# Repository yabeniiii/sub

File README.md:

# UUUV: Un-named Unmanned Underwater Vessel
early development

a remotely operated submarine

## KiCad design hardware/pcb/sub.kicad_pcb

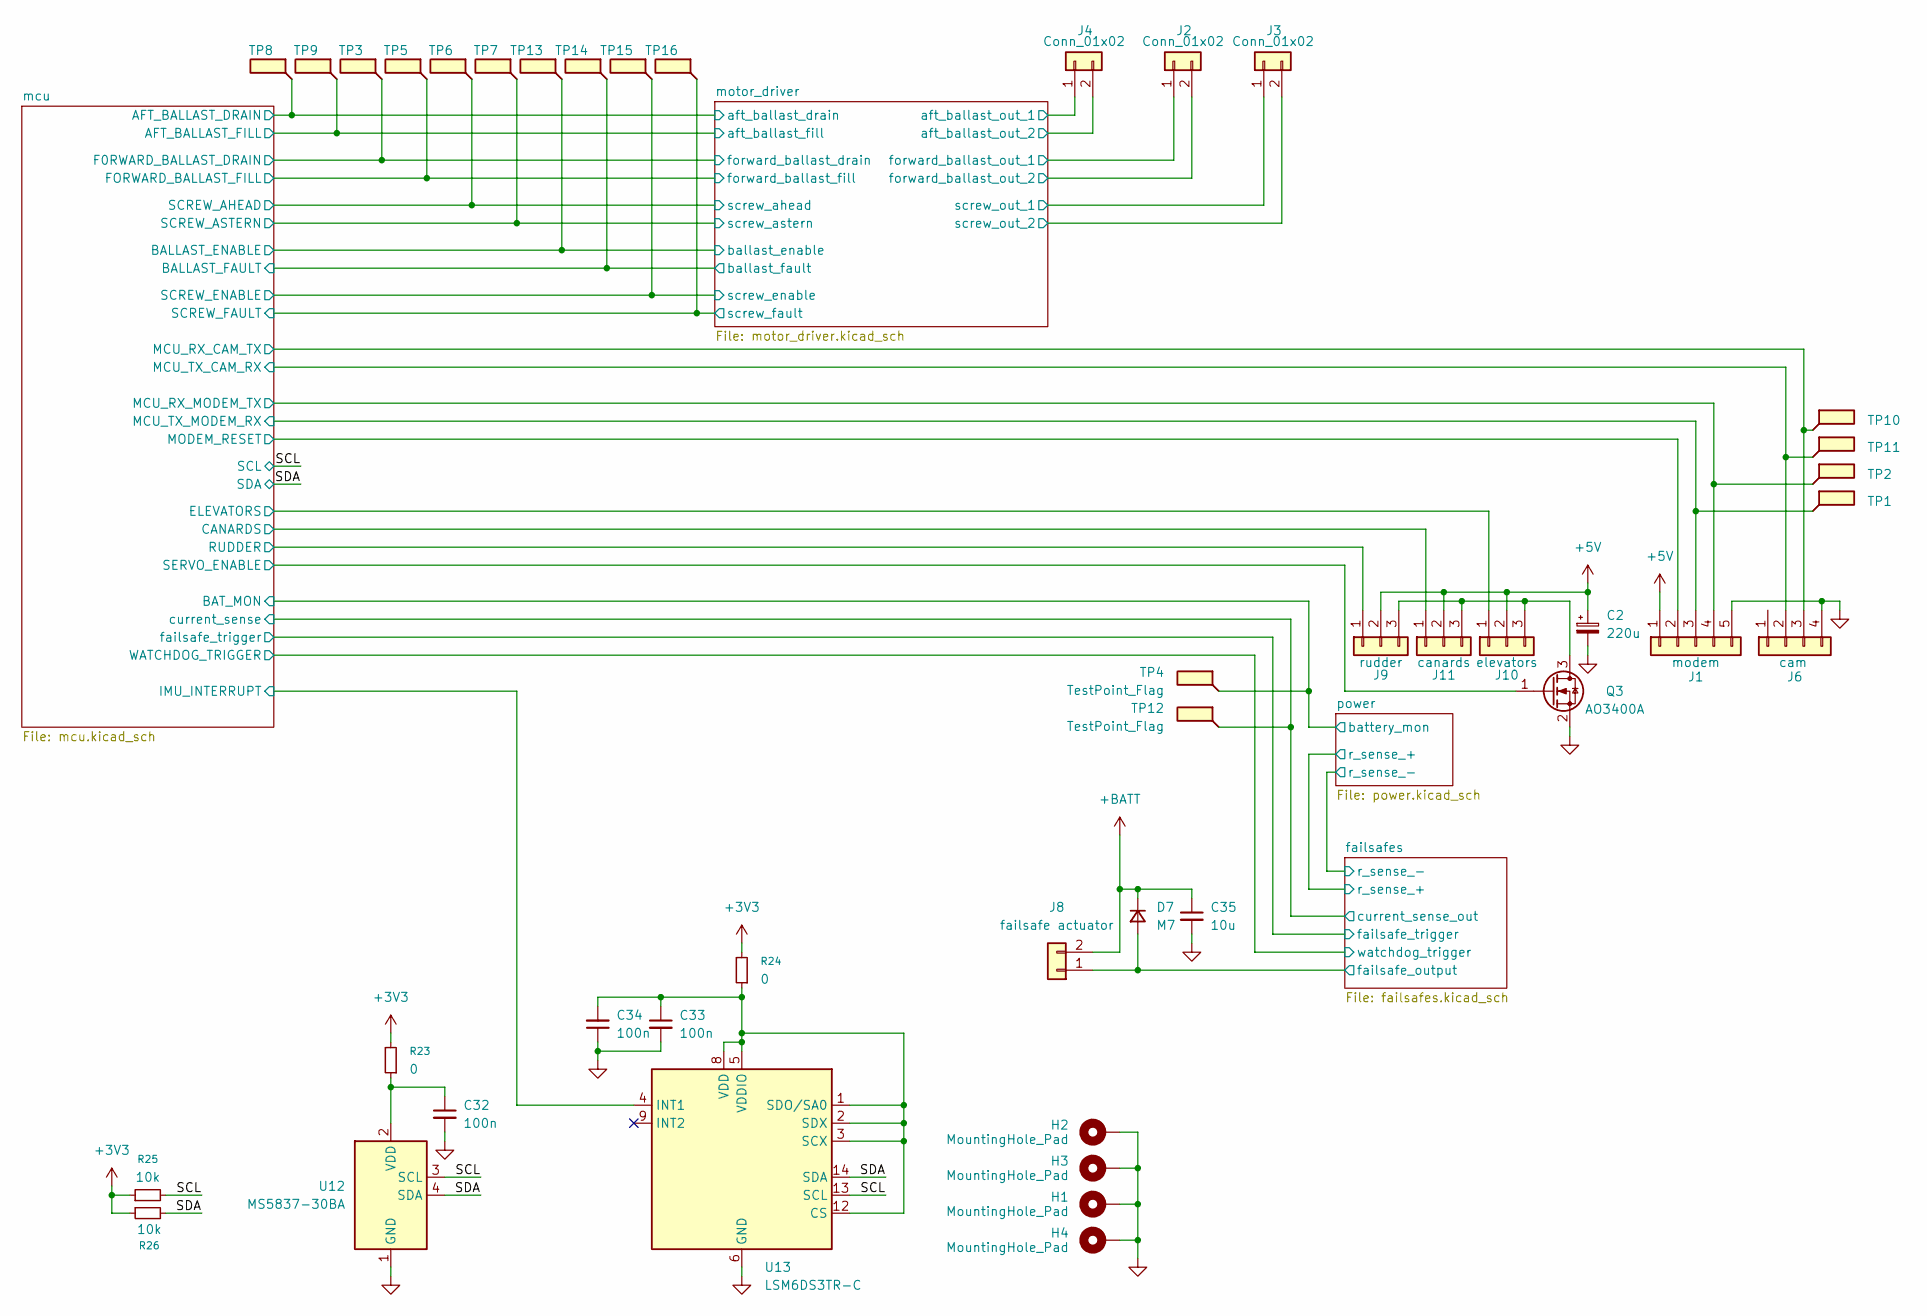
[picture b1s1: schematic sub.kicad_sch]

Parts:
C2: 220u; CP_Elec_6.3x7.7
C32, C33, C34: 100n; C_0805_2012Metric
C35: 10u; C_0805_2012Metric
D7: M7; D_SMA
H1, H2, H3, H4: MountingHole_Pad; MountingHole_2.2mm_M2_Pad_Via
J1: modem; Molex_PicoBlade_53047-0510_1x05_P1.25mm_Vertical
J2, J3, J4: Conn_01x02; Molex_PicoBlade_53047-0210_1x02_P1.25mm_Vertical
J6: cam; Molex_PicoBlade_53047-0410_1x04_P1.25mm_Vertical
J8: failsafe actuator; Molex_PicoBlade_53047-0210_1x02_P1.25mm_Vertical
J9: rudder; Molex_PicoBlade_53047-0310_1x03_P1.25mm_Vertical
J10: elevators; Molex_PicoBlade_53047-0310_1x03_P1.25mm_Vertical
J11: canards; Molex_PicoBlade_53047-0310_1x03_P1.25mm_Vertical
Q3: AO3400A; SOT-23
R23, R24: 0; R_0805_2012Metric
R25, R26: 10k; R_0805_2012Metric
TP1, TP2, TP4, TP10, TP11, TP12: TestPoint_Flag; TestPoint_Pad_D0.5
TP3, TP5, TP6, TP7, TP8, TP9, TP13, TP14, TP15, TP16: TestPoint_Pad_D0.5
U12: MS5837-30BA; TE_MS5837-xxBA
U13: LSM6DS3TR-C; LGA-14_3x2.5mm_P0.5mm_LayoutBorder3x4y

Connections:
+3V3: R23.2, R24.2, R25.1, R26.1; also elsewhere on the board
+5V: C2.1, J1.1, J9.2, J10.2, J11.2; also elsewhere on the board
+BATT: C35.1, D7.1 (K), J8.2; also elsewhere on the board
/SCL: R25.2, U12.3 (SCL), U13.13 (SCL); also elsewhere on the board
/SDA: R26.2, U12.4 (SDA), U13.14 (SDA); also elsewhere on the board
/failsafes/current_sense_out: TP12.1; also elsewhere on the board
/failsafes/failsafe_output: D7.2 (A), J8.1; also elsewhere on the board
/mcu/AFT_BALLAST_DRAIN: TP8.1; also elsewhere on the board
/mcu/AFT_BALLAST_FILL: TP9.1; also elsewhere on the board
/mcu/BAT_MON: TP4.1; also elsewhere on the board
/mcu/CANARDS: J11.1; also elsewhere on the board
/mcu/ELEVATORS: J10.1; also elsewhere on the board
/mcu/F0RWARD_BALLAST_DRAIN: TP3.1; also elsewhere on the board
/mcu/FORWARD_BALLAST_FILL: TP5.1; also elsewhere on the board
/mcu/IMU_INTERRUPT: U13.4 (INT1); also elsewhere on the board
/mcu/MCU_RX_CAM_TX: J6.3, TP10.1; also elsewhere on the board
/mcu/MCU_RX_MODEM_TX: J1.4, TP2.1; also elsewhere on the board
/mcu/MCU_TX_CAM_RX: J6.2, TP11.1; also elsewhere on the board
/mcu/MCU_TX_MODEM_RX: J1.3, TP1.1; also elsewhere on the board
/mcu/MODEM_RESET: J1.2; also elsewhere on the board
/mcu/RUDDER: J9.1; also elsewhere on the board
/mcu/SCREW_AHEAD: TP6.1; also elsewhere on the board
/mcu/SCREW_ASTERN: TP7.1; also elsewhere on the board
/mcu/SERVO_ENABLE: Q3.1 (G); also elsewhere on the board
/motor_driver/aft_ballast_out_1: J4.1; also elsewhere on the board
/motor_driver/aft_ballast_out_2: J4.2; also elsewhere on the board
/motor_driver/forward_ballast_out_1: J2.1; also elsewhere on the board
/motor_driver/forward_ballast_out_2: J2.2; also elsewhere on the board
/motor_driver/screw_out_1: J3.1; also elsewhere on the board
/motor_driver/screw_out_2: J3.2; also elsewhere on the board
GND: C2.2, C32.2, C33.2, C34.1, C35.2, H1.1, H2.1, H3.1, H4.1, J1.5, J6.4, Q3.2 (S), U12.1 (GND), U13.6 (GND), U13.7 (GND); also elsewhere on the board
unnamed: J9.3, J10.3, J11.3, Q3.3 (D)
unnamed: C32.1, R23.1, U12.2 (VDD)
unnamed: C33.1, C34.2, R24.1, U13.1 (SDO/SA0), U13.2 (SDX), U13.3 (SCX), U13.5 (VDDIO), U13.8 (VDD), U13.12 (CS)

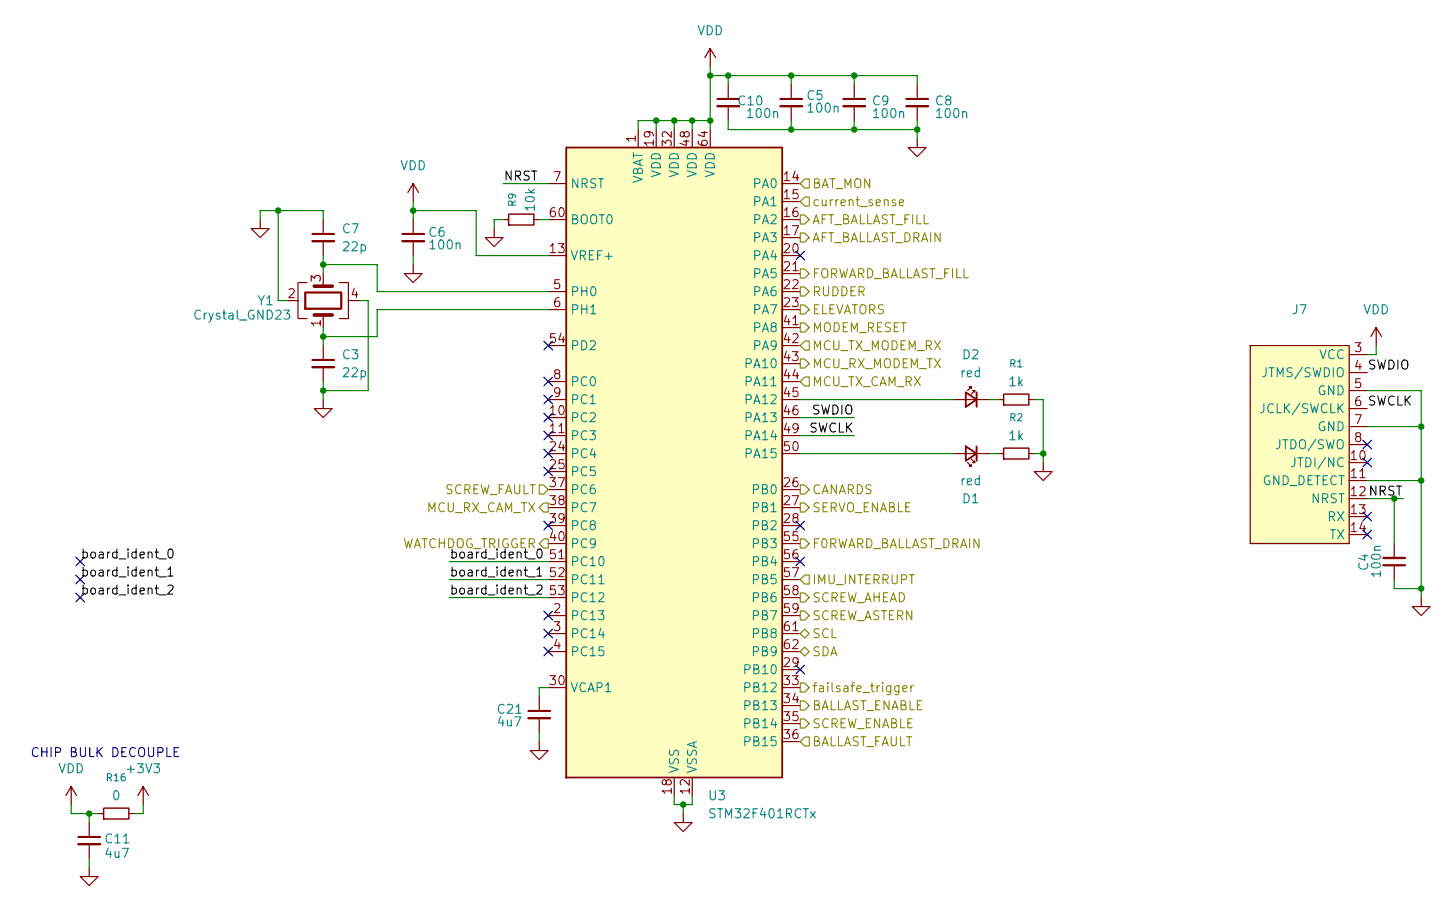
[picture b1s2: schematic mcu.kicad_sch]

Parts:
C3, C7: 22p; C_0805_2012Metric
C4, C5, C6, C8, C9, C10: 100n; C_0805_2012Metric
C11, C21: 4u7; C_0805_2012Metric
D1, D2: red; LED_1206_3216Metric
J7: PinHeader_2x07_P1.27mm_Vertical_SMD
R1, R2: 1k; R_0805_2012Metric
R9: 10k; R_0805_2012Metric
R16: 0; R_0805_2012Metric
U3: STM32F401RCTx; LQFP-64_10x10mm_P0.5mm
Y1: Crystal_GND23; Crystal_SMD_3225-4Pin_3.2x2.5mm

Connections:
+3V3: R16.2; also elsewhere on the board
/SCL: U3.61 (PB8); also elsewhere on the board
/SDA: U3.62 (PB9); also elsewhere on the board
/failsafes/current_sense_out: U3.15 (PA1); also elsewhere on the board
/failsafes/failsafe_trigger: U3.33 (PB12); also elsewhere on the board
/failsafes/watchdog_trigger: U3.40 (PC9); also elsewhere on the board
/mcu/AFT_BALLAST_DRAIN: U3.17 (PA3); also elsewhere on the board
/mcu/AFT_BALLAST_FILL: U3.16 (PA2); also elsewhere on the board
/mcu/BALLAST_ENABLE: U3.34 (PB13); also elsewhere on the board
/mcu/BALLAST_FAULT: U3.36 (PB15); also elsewhere on the board
/mcu/BAT_MON: U3.14 (PA0); also elsewhere on the board
/mcu/CANARDS: U3.26 (PB0); also elsewhere on the board
/mcu/ELEVATORS: U3.23 (PA7); also elsewhere on the board
/mcu/F0RWARD_BALLAST_DRAIN: U3.55 (PB3); also elsewhere on the board
/mcu/FORWARD_BALLAST_FILL: U3.21 (PA5); also elsewhere on the board
/mcu/IMU_INTERRUPT: U3.57 (PB5); also elsewhere on the board
/mcu/MCU_RX_CAM_TX: U3.38 (PC7); also elsewhere on the board
/mcu/MCU_RX_MODEM_TX: U3.43 (PA10); also elsewhere on the board
/mcu/MCU_TX_CAM_RX: U3.44 (PA11); also elsewhere on the board
/mcu/MCU_TX_MODEM_RX: U3.42 (PA9); also elsewhere on the board
/mcu/MODEM_RESET: U3.41 (PA8); also elsewhere on the board
/mcu/NRST: C4.2, J7.12 (NRST), U3.7 (NRST)
/mcu/RUDDER: U3.22 (PA6); also elsewhere on the board
/mcu/SCREW_AHEAD: U3.58 (PB6); also elsewhere on the board
/mcu/SCREW_ASTERN: U3.59 (PB7); also elsewhere on the board
/mcu/SCREW_ENABLE: U3.35 (PB14); also elsewhere on the board
/mcu/SCREW_FAULT: U3.37 (PC6); also elsewhere on the board
/mcu/SERVO_ENABLE: U3.27 (PB1); also elsewhere on the board
/mcu/SWCLK: J7.6 (JCLK/SWCLK), U3.49 (PA14)
/mcu/SWDIO: J7.4 (JTMS/SWDIO), U3.46 (PA13)
/mcu/board_ident_0: U3.51 (PC10)
/mcu/board_ident_1: U3.52 (PC11)
/mcu/board_ident_2: U3.53 (PC12)
GND: C3.2, C4.1, C5.2, C6.2, C7.1, C8.2, C9.2, C10.2, C11.2, C21.2, J7.5 (GND), J7.7 (GND), J7.11 (GND_DETECT), R1.2, R2.2, R9.1, U3.12 (VSSA), U3.18 (VSS), U3.31 (VSS), U3.47 (VSS), U3.63 (VSS), Y1.2, Y1.4; also elsewhere on the board
unnamed: D1.2 (A), U3.50 (PA15)
unnamed: D1.1 (K), R2.1
unnamed: D2.2 (A), U3.45 (PA12)
unnamed: D2.1 (K), R1.1
unnamed: R9.2, U3.60 (BOOT0)
unnamed: C7.2, U3.5 (PH0), Y1.3
unnamed: C3.1, U3.6 (PH1), Y1.1
unnamed: C21.1, U3.30 (VCAP1)
VDD: C5.1, C6.1, C8.1, C9.1, C10.1, C11.1, J7.3 (VCC), R16.1, U3.1 (VBAT), U3.13 (VREF+), U3.19 (VDD), U3.32 (VDD), U3.48 (VDD), U3.64 (VDD)

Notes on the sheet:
CHIP BULK DECOUPLE

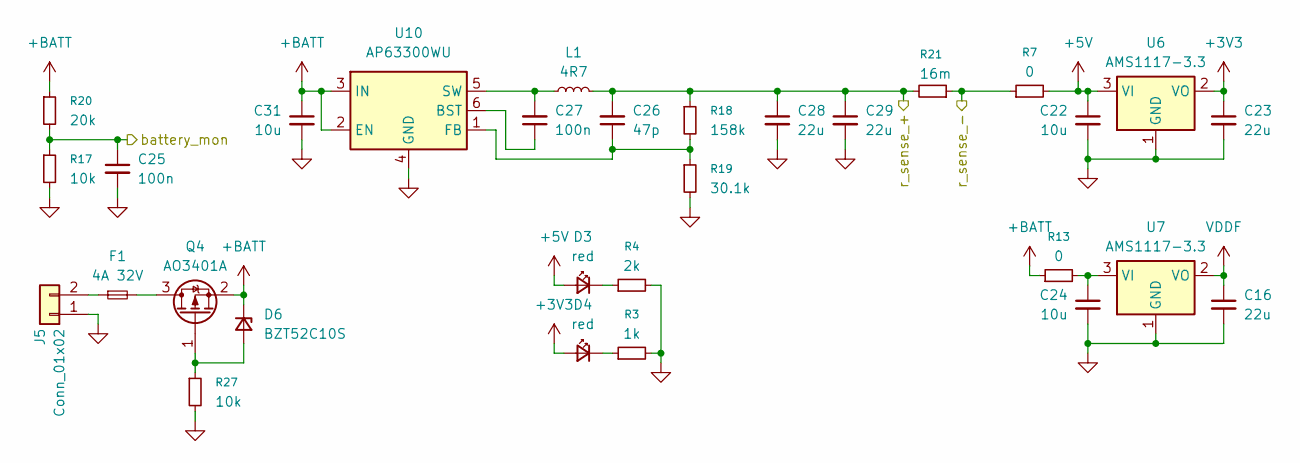
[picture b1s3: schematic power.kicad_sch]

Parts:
C16, C23, C28, C29: 22u; C_0805_2012Metric
C22, C24, C31: 10u; C_0805_2012Metric
C25, C27: 100n; C_0805_2012Metric
C26: 47p; C_0805_2012Metric
D3, D4: red; LED_1206_3216Metric
D6: BZT52C10S; D_SOD-323
F1: 4A 32V; Fuse_1206_3216Metric
J5: Conn_01x02; AMASS_XT30U-F_1x02_P5.0mm_Vertical
L1: 4R7; L_10.4x10.4_H4.8
Q4: AO3401A; SOT-23
R3: 1k; R_0805_2012Metric
R4: 2k; R_0805_2012Metric
R7, R13: 0; R_0805_2012Metric
R17, R27: 10k; R_0805_2012Metric
R18: 158k; R_0805_2012Metric
R19: 30.1k; R_0805_2012Metric
R20: 20k; R_0805_2012Metric
R21: 16m; R_0805_2012Metric
U6, U7: AMS1117-3.3; SOT-89-3
U10: AP63300WU; TSOT-23-6

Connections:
+3V3: C23.1, D4.2 (A), U6.2 (VO); also elsewhere on the board
+5V: C22.1, D3.2 (A), R7.2, U6.3 (VI); also elsewhere on the board
+BATT: C31.1, D6.1 (K), Q4.2 (S), R13.1, R20.1, U10.2 (EN), U10.3 (IN); also elsewhere on the board
/failsafes/r_sense_+: C26.2, C28.1, C29.1, L1.2, R18.1, R21.2; also elsewhere on the board
/failsafes/r_sense_-: R7.1, R21.1; also elsewhere on the board
/mcu/BAT_MON: C25.1, R17.1, R20.2; also elsewhere on the board
GND: C16.2, C22.2, C23.2, C24.2, C25.2, C28.2, C29.2, C31.2, J5.1, R3.2, R4.2, R17.2, R19.2, R27.2, U6.1 (GND), U7.1 (GND), U10.4 (GND); also elsewhere on the board
unnamed: D3.1 (K), R4.1
unnamed: D4.1 (K), R3.1
unnamed: D6.2 (A), Q4.1 (G), R27.1
unnamed: F1.1, J5.2
unnamed: F1.2, Q4.3 (D)
unnamed: C24.1, R13.2, U7.3 (VI)
unnamed: C27.1, U10.6 (BST)
unnamed: C26.1, R18.2, R19.1, U10.1 (FB)
unnamed: C27.2, L1.1, U10.5 (SW)
VDDF: C16.1, U7.2 (VO); also elsewhere on the board

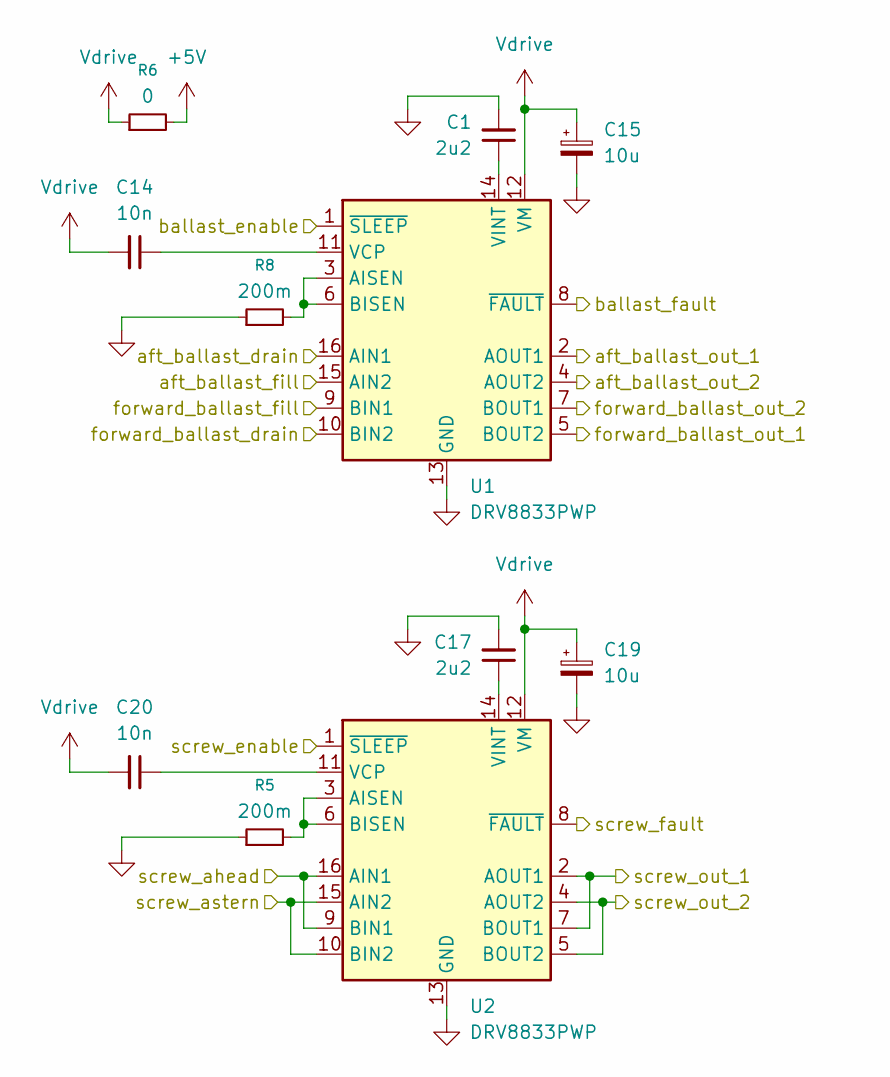
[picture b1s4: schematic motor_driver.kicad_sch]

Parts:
C1, C17: 2u2; C_0805_2012Metric
C14, C20: 10n; C_0805_2012Metric
C15, C19: 10u; C_0805_2012Metric
R5, R8: 200m; R_0805_2012Metric
R6: 0; R_0805_2012Metric
U1, U2: DRV8833PWP; HTSSOP-16-1EP_4.4x5mm_P0.65mm_EP3.4x5mm_Mask2.46x2.31mm_The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

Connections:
+5V: R6.2; also elsewhere on the board
/mcu/AFT_BALLAST_DRAIN: U1.16 (AIN1); also elsewhere on the board
/mcu/AFT_BALLAST_FILL: U1.15 (AIN2); also elsewhere on the board
/mcu/BALLAST_ENABLE: U1.1 (~SLEEP); also elsewhere on the board
/mcu/BALLAST_FAULT: U1.8 (~FAULT); also elsewhere on the board
/mcu/F0RWARD_BALLAST_DRAIN: U1.10 (BIN2); also elsewhere on the board
/mcu/FORWARD_BALLAST_FILL: U1.9 (BIN1); also elsewhere on the board
/mcu/SCREW_AHEAD: U2.9 (BIN1), U2.16 (AIN1); also elsewhere on the board
/mcu/SCREW_ASTERN: U2.10 (BIN2), U2.15 (AIN2); also elsewhere on the board
/mcu/SCREW_ENABLE: U2.1 (~SLEEP); also elsewhere on the board
/mcu/SCREW_FAULT: U2.8 (~FAULT); also elsewhere on the board
/motor_driver/aft_ballast_out_1: U1.2 (AOUT1); also elsewhere on the board
/motor_driver/aft_ballast_out_2: U1.4 (AOUT2); also elsewhere on the board
/motor_driver/forward_ballast_out_1: U1.5 (BOUT2); also elsewhere on the board
/motor_driver/forward_ballast_out_2: U1.7 (BOUT1); also elsewhere on the board
/motor_driver/screw_out_1: U2.2 (AOUT1), U2.7 (BOUT1); also elsewhere on the board
/motor_driver/screw_out_2: U2.4 (AOUT2), U2.5 (BOUT2); also elsewhere on the board
GND: C1.2, C15.2, C17.2, C19.2, R5.1, R8.1, U1.13 (GND), U1.17 (GND), U2.13 (GND), U2.17 (GND); also elsewhere on the board
unnamed: R8.2, U1.3 (AISEN), U1.6 (BISEN)
unnamed: C14.1, U1.11 (VCP)
unnamed: C1.1, U1.14 (VINT)
unnamed: R5.2, U2.3 (AISEN), U2.6 (BISEN)
unnamed: C20.1, U2.11 (VCP)
unnamed: C17.1, U2.14 (VINT)
Vdrive: C14.2, C15.1, C19.1, C20.2, R6.1, U1.12 (VM), U2.12 (VM)

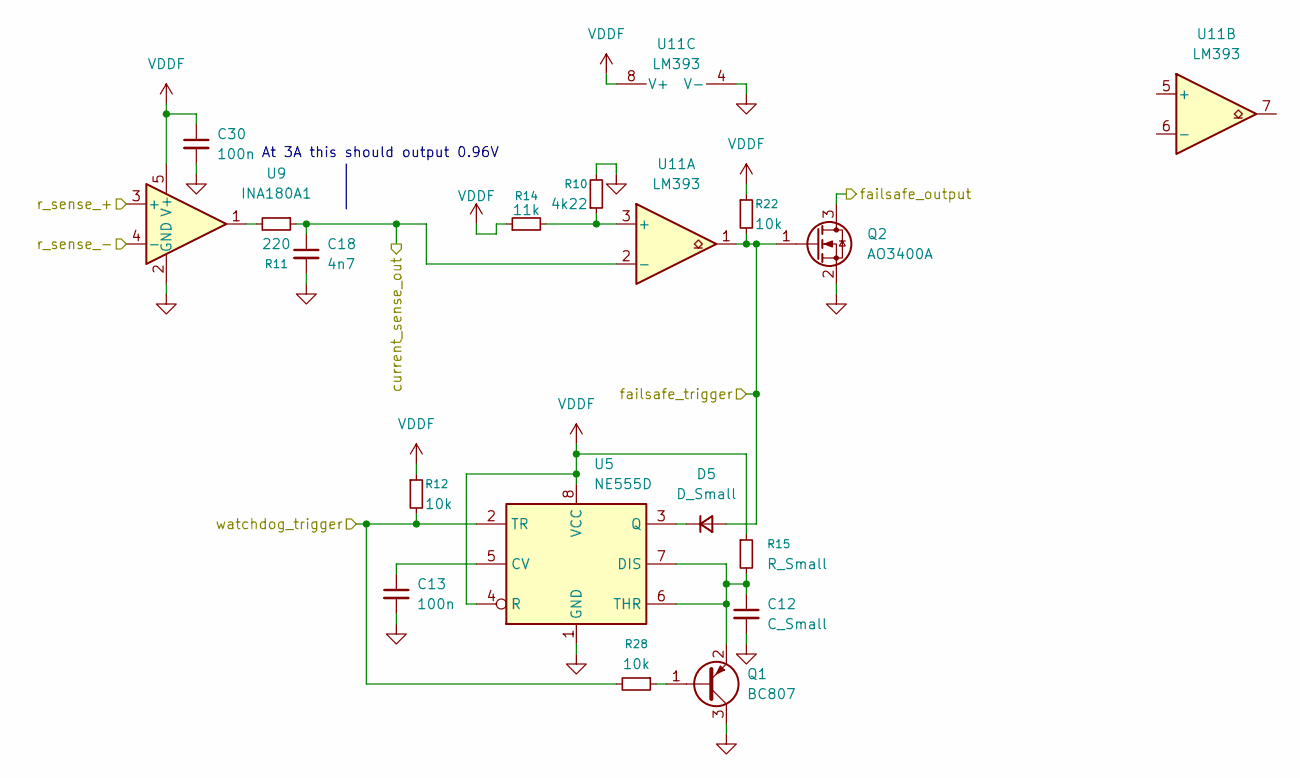
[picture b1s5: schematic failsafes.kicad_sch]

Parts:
C12: C_Small; C_0805_2012Metric
C13, C30: 100n; C_0805_2012Metric
C18: 4n7; C_0805_2012Metric
D5: D_Small; D_MiniMELF
Q1: BC807; SOT-23
Q2: AO3400A; SOT-23
R10: 4k22; R_0805_2012Metric
R11: 220; R_0805_2012Metric
R12, R22, R28: 10k; R_0805_2012Metric
R14: 11k; R_0805_2012Metric
R15: R_Small; R_0805_2012Metric
U5: NE555D; SOIC-8_3.9x4.9mm_P1.27mm
U9: INA180A1; SOT-23-5
U11: LM393; SOIC-8_3.9x4.9mm_P1.27mm

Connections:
/failsafes/current_sense_out: C18.1, R11.1, U11.2 (-); also elsewhere on the board
/failsafes/failsafe_output: Q2.3 (D); also elsewhere on the board
/failsafes/failsafe_trigger: D5.2 (A), Q2.1 (G), R22.2, U11.1; also elsewhere on the board
/failsafes/r_sense_+: U9.3 (+); also elsewhere on the board
/failsafes/r_sense_-: U9.4 (-); also elsewhere on the board
/failsafes/watchdog_trigger: R12.2, R28.2, U5.2 (TR); also elsewhere on the board
GND: C12.2, C13.2, C18.2, C30.2, Q1.3 (C), Q2.2 (S), R10.2, U5.1 (GND), U9.2 (GND), U11.4 (V-); also elsewhere on the board
unnamed: D5.1 (K), U5.3 (Q)
unnamed: Q1.1 (B), R28.1
unnamed: C12.1, Q1.2 (E), R15.2, U5.6 (THR), U5.7 (DIS)
unnamed: R11.2, U9.1
unnamed: C13.1, U5.5 (CV)
unnamed: R10.1, R14.2, U11.3 (+)
VDDF: C30.1, R12.1, R14.1, R15.1, R22.1, U5.4 (R), U5.8 (VCC), U9.5 (V+), U11.8 (V+); also elsewhere on the board

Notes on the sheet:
At 3A this should output 0.96V

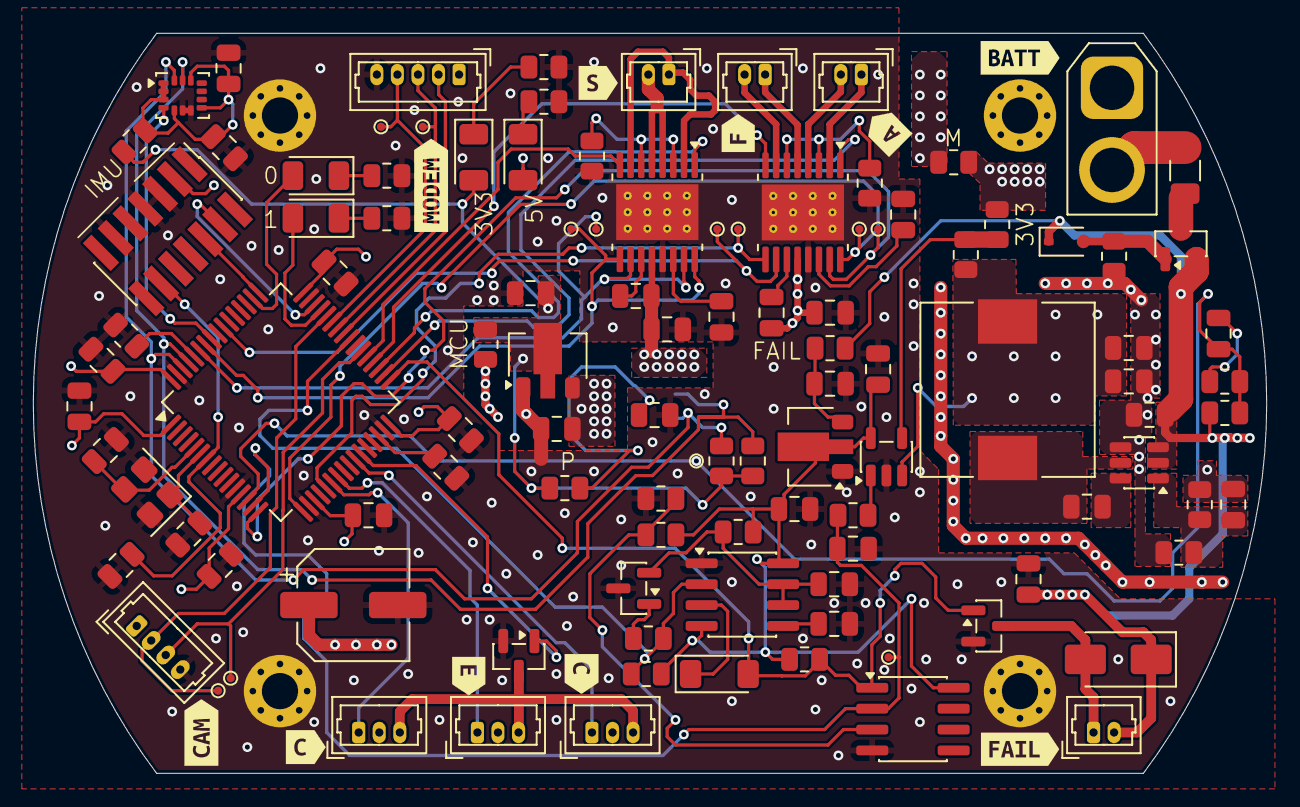
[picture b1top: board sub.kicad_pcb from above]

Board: 4 copper layers, 75.0 x 45.0 mm, 125 parts (1 on the bottom side), 77 nets.

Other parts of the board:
kibuzzard-6ADA83F7: G***; kibuzzard-6ADA83F7
kibuzzard-6ADA85B6: G***; kibuzzard-6ADA85B6
kibuzzard-6ADA85C5: G***; kibuzzard-6ADA85C5
kibuzzard-6ADA85E6: G***; kibuzzard-6ADA85E6
kibuzzard-6ADA849A: G***; kibuzzard-6ADA849A
kibuzzard-6ADA851D: G***; kibuzzard-6ADA851D
kibuzzard-6ADA859F: G***; kibuzzard-6ADA859F
kibuzzard-6ADA8528: G***; kibuzzard-6ADA8528
kibuzzard-6AE0F408: G***; kibuzzard-6AE0F408
kibuzzard-6AE0FBA1: G***; kibuzzard-6AE0FBA1

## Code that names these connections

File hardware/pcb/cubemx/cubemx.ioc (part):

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Mcu.Name=STM32F401R(B-C)Tx
Mcu.Package=LQFP64
Mcu.UserName=STM32F401RCTx
PA0-WKUP.GPIOParameters=GPIO_Label
PA0-WKUP.GPIO_Label=battery_adc
PA0-WKUP.Signal=ADCx_IN0
PA10.GPIOParameters=GPIO_Label
PA10.GPIO_Label=modem_usart_rx
PA10.Mode=Asynchronous
PA10.Signal=USART1_RX
PA13.Mode=Serial_Wire
PA13.Signal=SYS_JTMS-SWDIO
PA14.Mode=Serial_Wire
PA14.Signal=SYS_JTCK-SWCLK
PA2.GPIOParameters=GPIO_Label
PA2.GPIO_Label=cam_usart_tx
PA2.Mode=Asynchronous
PA2.Signal=USART2_TX
PA3.GPIOParameters=GPIO_Label
PA3.GPIO_Label=cam_usart_rx
PA3.Mode=Asynchronous
PA3.Signal=USART2_RX
PA6.GPIOParameters=GPIO_Label
PA6.GPIO_Label=rudder
PA6.Signal=S_TIM3_CH1
PA7.GPIOParameters=GPIO_Label
PA7.GPIO_Label=elevator
PA7.Signal=S_TIM3_CH2
PA8.GPIOParameters=GPIO_Label
PA8.GPIO_Label=esp_rst
PA8.Signal=GPIO_Output
PA9.GPIOParameters=GPIO_Label
PA9.GPIO_Label=modem_usart_tx
PA9.Mode=Asynchronous
PA9.Signal=USART1_TX
PB0.GPIOParameters=GPIO_Label
PB0.GPIO_Label=canard
PB0.Signal=S_TIM3_CH3
PB1.GPIOParameters=GPIO_Label
PB1.GPIO_Label=screw
PB1.Signal=S_TIM3_CH4
PB13.GPIOParameters=GPIO_Label
PB13.GPIO_Label=forward_ballast_drain
PB13.Signal=GPIO_Output
PB14.GPIOParameters=GPIO_Label
PB14.GPIO_Label=forward_ballast_fill
PB14.Signal=GPIO_Output
PB15.GPIOParameters=GPIO_Label
PB15.GPIO_Label=aft_ballast_drain
PB15.Signal=GPIO_Output
PB6.Mode=I2C
PB6.Signal=I2C1_SCL
PB7.Mode=I2C
PB7.Signal=I2C1_SDA
PC6.GPIOParameters=GPIO_Label
PC6.GPIO_Label=aft_ballast_fill
PC6.Signal=GPIO_Output
PH0\ -\ OSC_IN.Mode=HSE-External-Oscillator
PH0\ -\ OSC_IN.Signal=RCC_OSC_IN
PH1\ -\ OSC_OUT.Mode=HSE-External-Oscillator
PH1\ -\ OSC_OUT.Signal=RCC_OSC_OUT
RCC.HSE_VALUE=24000000
RCC.SYSCLKFreq_VALUE=84000000
RCC.SYSCLKSource=RCC_SYSCLKSOURCE_PLLCLK
board=custom
